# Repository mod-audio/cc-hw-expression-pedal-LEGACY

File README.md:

Legacy mod-hw-expression-pedal
=======================

This repository contains the schematics and PCB design files for the Expression Pedal hardware.
This is a peripheral meant to be used in conjunction with MOD (http://moddevices.com/) via its control-chain interface.

These files were created and can be improved with KiCAD, a free software Electronics CAD which is available at http://www.kicad-pcb.org/

## Check out instructions ##

This project uses a set of KiCAD symbols and footprints provided by the official KiCad library (https://github.com/KiCad/). In order to properly fetch these dependencies, which are configured as submodule repositories, you have to use the **--recursive** attribute in the following **git** command:

> git clone --recursive https://github.com/mod-audio/cc-hw-expression-pedal-LEGACY.git

## Licensing ##

Copyright (c) 2014-2026 MOD Audio Limited.

The hardware design files (schematics, PCB layouts, fabrication files, BOMs) are licensed under
[CC BY-SA 4.0](https://creativecommons.org/licenses/by-sa/4.0/) (see [`LICENSE`](LICENSE)).
This is an open hardware project: you may use, modify, build and sell it, as long as you credit MOD Audio
and share your modified design files under the same licence.

Third-party files (manufacturer component models, library parts, supplier documents) are not covered by
this licence. See [`NOTICE`](NOTICE) for the list.

The MOD logo is a registered trademark (EU trade mark no. 016228827; UK trade mark no. UK00916228827).
The licence gives no right to use the MOD name or logo. See [`NOTICE`](NOTICE).

## Firmware ##

The firmware is kept in a separate repository and is not part of this one.

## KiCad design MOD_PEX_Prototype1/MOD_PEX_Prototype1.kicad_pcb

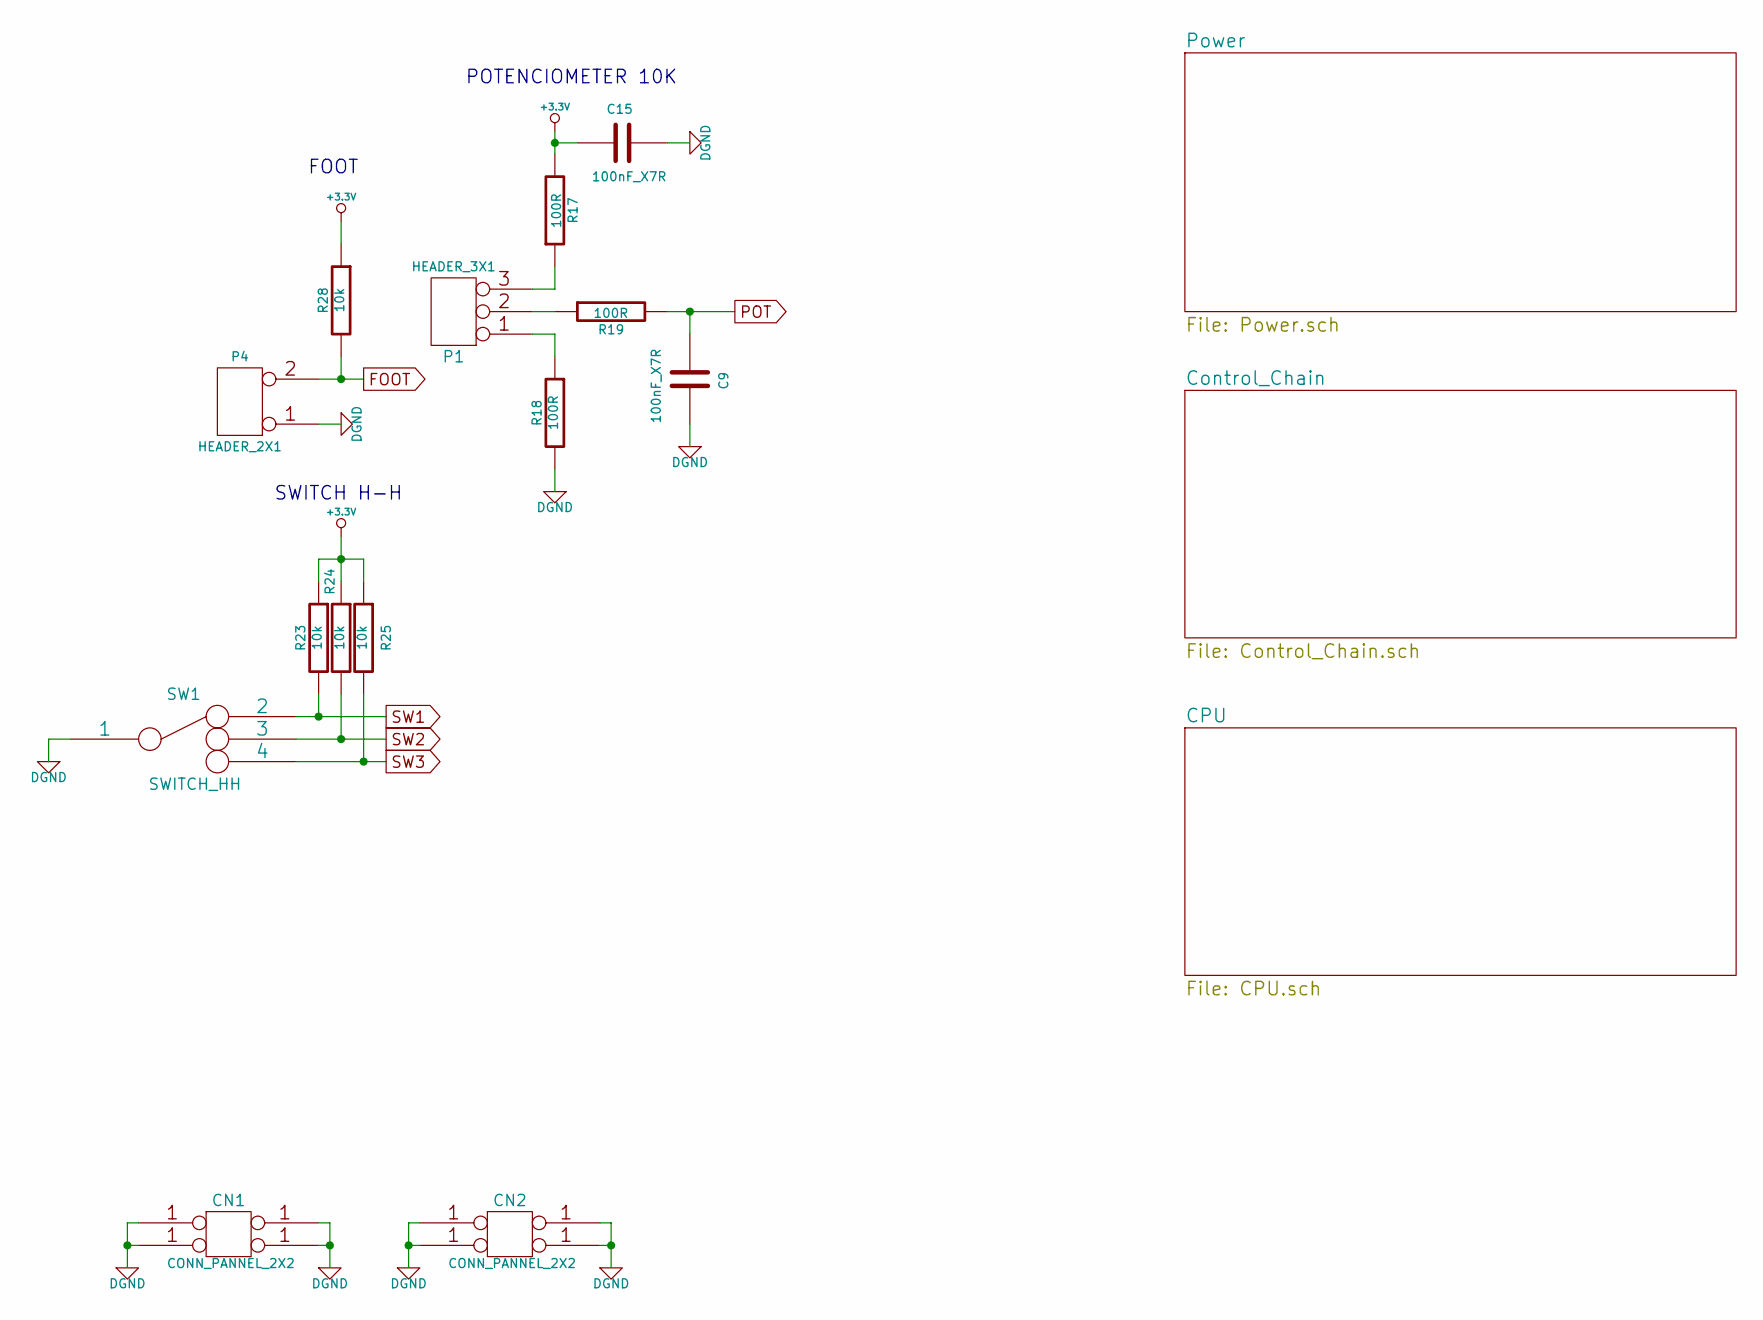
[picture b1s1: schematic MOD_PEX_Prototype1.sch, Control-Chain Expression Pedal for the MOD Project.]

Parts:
C9, C15: 100nF_X7R; SM0603
CN1, CN2: CONN_PANNEL_2X2; CONN_PANNEL
P1: HEADER_3X1; PIN_ARRAY_3X1
P4: HEADER_2X1; PIN_ARRAY_2X1
R17, R18, R19: 100R; SM0603
R23, R24, R25, R28: 10k; SM0603
SW1: SWITCH_HH; SWITCH_HH_SK-13D26-G-6_5-K-GY

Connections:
DGND: C9.2, C15.2, CN1.1, CN2.1, P4.1, R18.2, SW1.1; also elsewhere on the board
FOOT: P4.2 (PM), R28.2; also elsewhere on the board
unnamed: P1.1, R18.1
unnamed: P1.2 (PM), R19.1
unnamed: P1.3, R17.1
POT: C9.1, R19.2; also elsewhere on the board
SW1: R23.2, SW1.2; also elsewhere on the board
SW2: R24.2, SW1.3; also elsewhere on the board
SW3: R25.2, SW1.4; also elsewhere on the board

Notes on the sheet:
POTENCIOMETER 10K
SWITCH H-H
FOOT

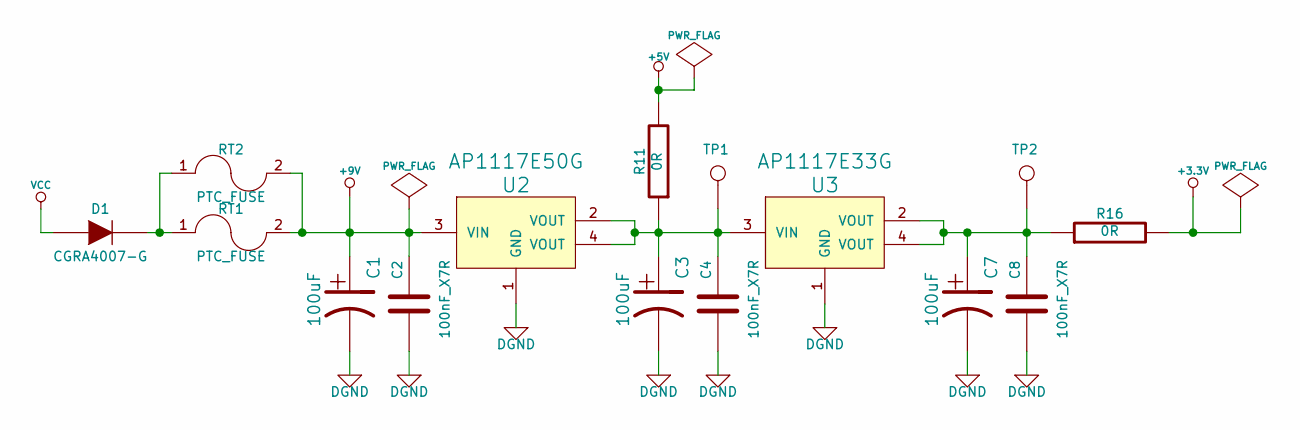
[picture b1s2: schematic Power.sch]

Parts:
C1, C3, C7: 100uF; CAP_RAD_5MM
C2, C4, C8: 100nF_X7R; SM0603
D1: CGRA4007-G; DO-214AC(SMA)
R11, R16: 0R; SM0805
RT1: PTC_FUSE; SM1210
RT2: PTC_FUSE; SM2920
TP1, TP2: CONN_1; SIL-1
U2: AP1117E50G; SOT223_3
U3: AP1117E33G; SOT223_3

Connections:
+5V: R11.2; also elsewhere on the board
+9V: C1.1, C2.1, RT1.2, RT2.2, U2.3 (VIN)
DGND: C1.2, C2.2, C3.2, C4.2, C7.2, C8.2, U2.1 (GND), U3.1 (GND); also elsewhere on the board
unnamed: C3.1, C4.1, R11.1, TP1.1, U2.2 (VOUT), U2.4 (VOUT), U3.3 (VIN)
unnamed: C7.1, C8.1, R16.1, TP2.1, U3.2 (VOUT), U3.4 (VOUT)
unnamed: D1.2 (K), RT1.1, RT2.1
VCC: D1.1 (A); also elsewhere on the board

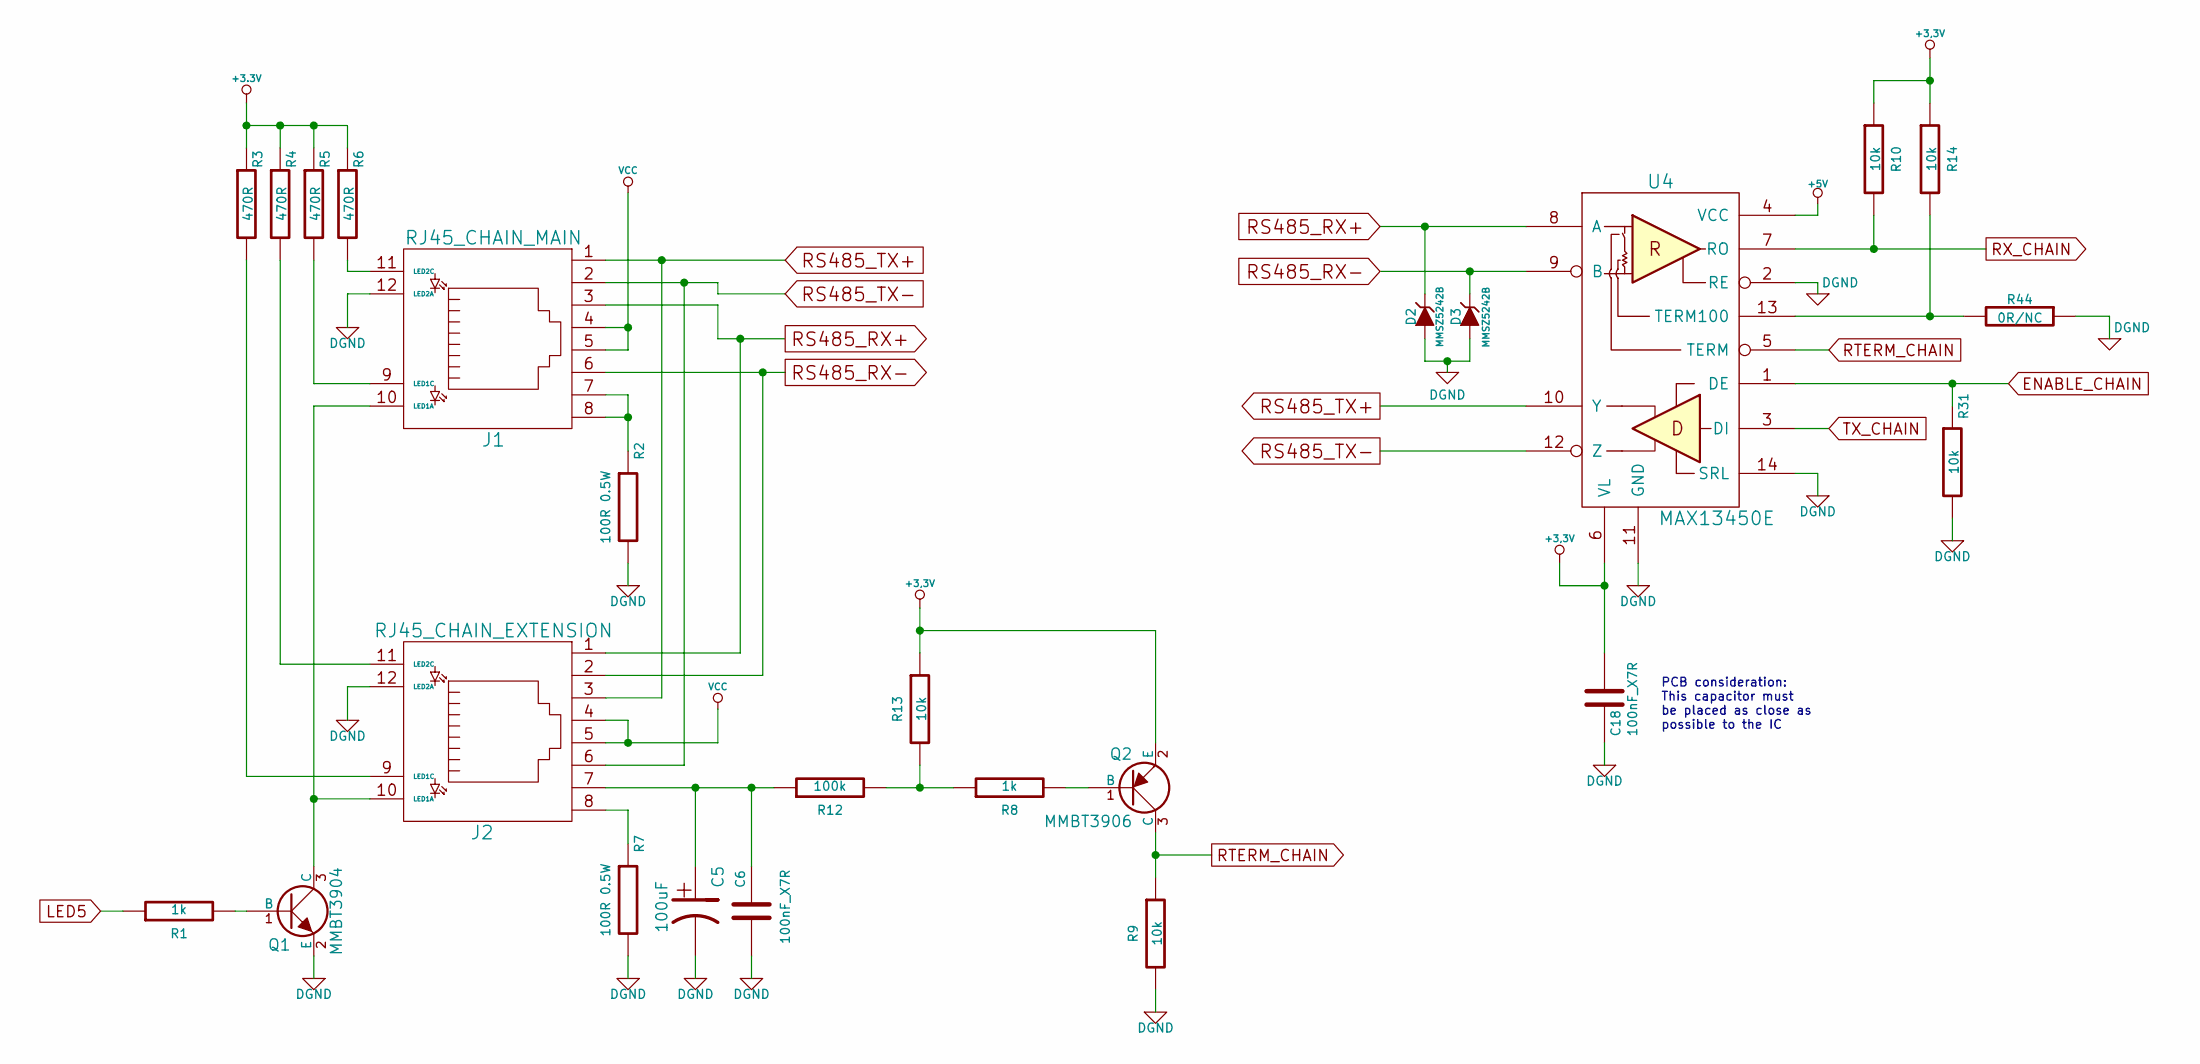
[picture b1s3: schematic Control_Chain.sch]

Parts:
C5: 100uF; CAP_RAD_5MM
C6, C18: 100nF_X7R; SM0603
D2, D3: MMSZ5242B; SOD123
J1: RJ45_CHAIN_MAIN; RJ45-RJHSE5084
J2: RJ45_CHAIN_EXTENSION; RJ45-RJHSE5084
Q1: MMBT3904; SOT23
Q2: MMBT3906; SOT23
R1, R8: 1k; SM0603
R2, R7: 100R 0.5W; SM1210
R3, R4, R5, R6: 470R; SM0805
R9, R10, R13, R14, R31: 10k; SM0603
R12: 100k; SM0603
R44: 0R/NC; SM0805
U4: MAX13450E; TSSOP14

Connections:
+5V: U4.4 (VCC); also elsewhere on the board
DGND: C5.2, C6.2, C18.2, D2.1 (A), D3.1 (A), J1.12 (LED2A), J2.12 (LED2A), Q1.2 (E), R2.2, R7.2, R9.2, R31.2, R44.1, U4.2 (RE), U4.11 (GND), U4.14 (SRL); also elsewhere on the board
ENABLE_CHAIN: R31.1, U4.1 (DE); also elsewhere on the board
LED5: R1.1
unnamed: C5.1, C6.1, J2.7, R12.1
unnamed: J1.7, J1.8, R2.1
unnamed: J1.9 (LED1C), R5.2
unnamed: J1.10 (LED1A), J2.10 (LED1A), Q1.3 (C)
unnamed: J1.11 (LED2C), R6.2
unnamed: J2.8, R7.1
unnamed: J2.9 (LED1C), R3.2
unnamed: J2.11 (LED2C), R4.2
unnamed: Q1.1 (B), R1.2
unnamed: Q2.1 (B), R8.2
unnamed: R8.1, R12.2, R13.2
unnamed: R14.2, R44.2, U4.13 (TERM100)
RS485_RX+: D2.2 (K), J1.3, J2.1, U4.8 (A)
RS485_RX-: D3.2 (K), J1.6, J2.2, U4.9 (B)
RS485_TX+: J1.1, J2.3, U4.10 (Y)
RS485_TX-: J1.2, J2.6, U4.12 (Z)
RTERM_CHAIN: Q2.3 (C), R9.1, U4.5 (TERM)
RX_CHAIN: R10.2, U4.7 (RO); also elsewhere on the board
TX_CHAIN: U4.3 (DI); also elsewhere on the board
VCC: J1.4, J1.5, J2.4, J2.5; also elsewhere on the board

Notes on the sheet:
PCB consideration: This capacitor must be placed as close as possible to the IC

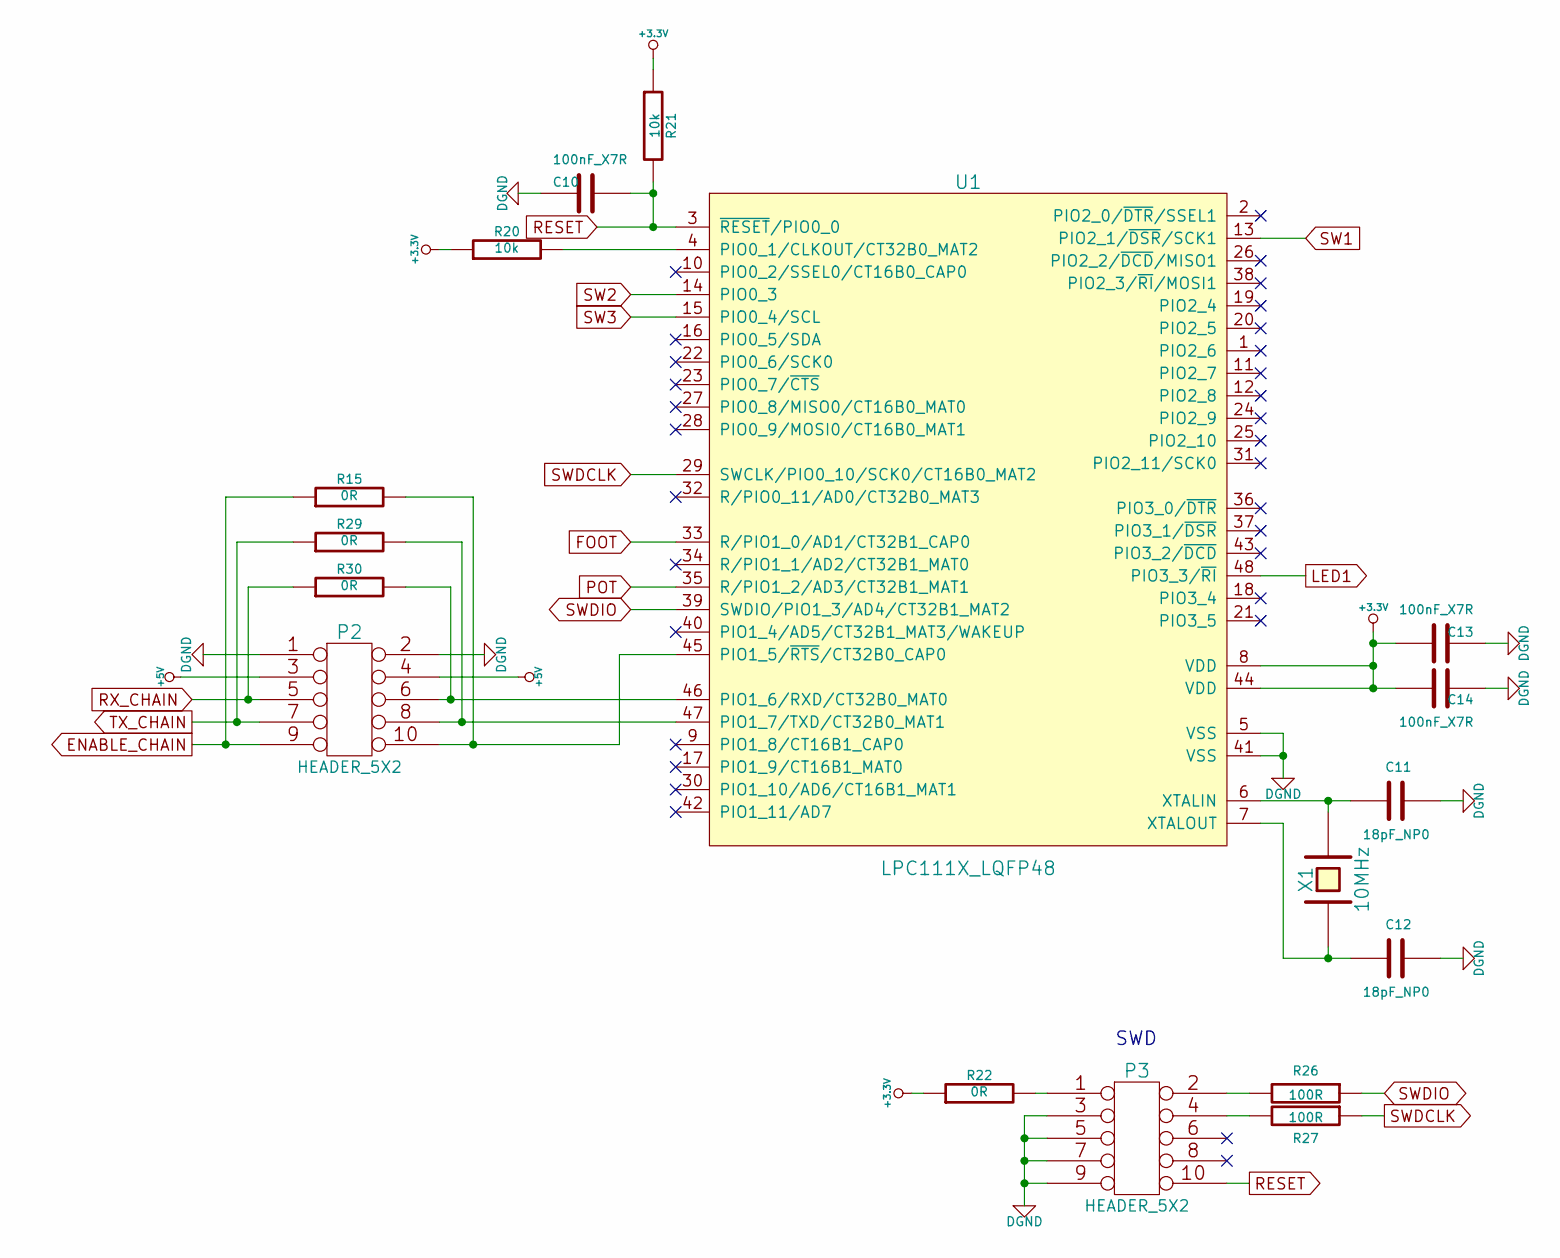
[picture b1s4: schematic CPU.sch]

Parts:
C10, C13, C14: 100nF_X7R; SM0603
C11, C12: 18pF_NP0; SM0603
P2, P3: HEADER_5X2; PIN_ARRAY_5x2
R15, R22, R29, R30: 0R; SM0603
R20, R21: 10k; SM0603
R26, R27: 100R; SM0603
U1: LPC111X_LQFP48; LQFP48
X1: 10MHz; HC_49US

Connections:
+5V: P2.3, P2.4; also elsewhere on the board
DGND: C10.2, C11.1, C12.1, C13.2, C14.2, P2.1, P2.2, P3.3, P3.5, P3.7, P3.9, U1.5 (VSS), U1.41 (VSS); also elsewhere on the board
ENABLE_CHAIN: P2.9, R15.1; also elsewhere on the board
FOOT: U1.33 (R/PIO1_0/AD1/CT32B1_CAP0); also elsewhere on the board
LED1: U1.48 (PIO3_3/~RI)
unnamed: C11.2, U1.6 (XTALIN), X1.2
unnamed: C12.2, U1.7 (XTALOUT), X1.1
unnamed: P2.6, R30.2, U1.46 (PIO1_6/RXD/CT32B0_MAT0)
unnamed: P2.8, R29.2, U1.47 (PIO1_7/TXD/CT32B0_MAT1)
unnamed: P2.10, R15.2, U1.45 (PIO1_5/~RTS~/CT32B0_CAP0)
unnamed: P3.1, R22.2
unnamed: P3.2, R26.2
unnamed: P3.4, R27.2
unnamed: R20.2, U1.4 (PIO0_1/CLKOUT/CT32B0_MAT2)
POT: U1.35 (R/PIO1_2/AD3/CT32B1_MAT1); also elsewhere on the board
RESET: C10.1, P3.10, R21.2, U1.3 (~RESET~/PIO0_0)
RX_CHAIN: P2.5, R30.1; also elsewhere on the board
SW1: U1.13 (PIO2_1/~DSR~/SCK1); also elsewhere on the board
SW2: U1.14 (PIO0_3); also elsewhere on the board
SW3: U1.15 (PIO0_4/SCL); also elsewhere on the board
SWDCLK: R27.1, U1.29 (SWCLK/PIO0_10/SCK0/CT16B0_MAT2)
SWDIO: R26.1, U1.39 (SWDIO/PIO1_3/AD4/CT32B1_MAT2)
TX_CHAIN: P2.7, R29.1; also elsewhere on the board

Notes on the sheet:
SWD

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
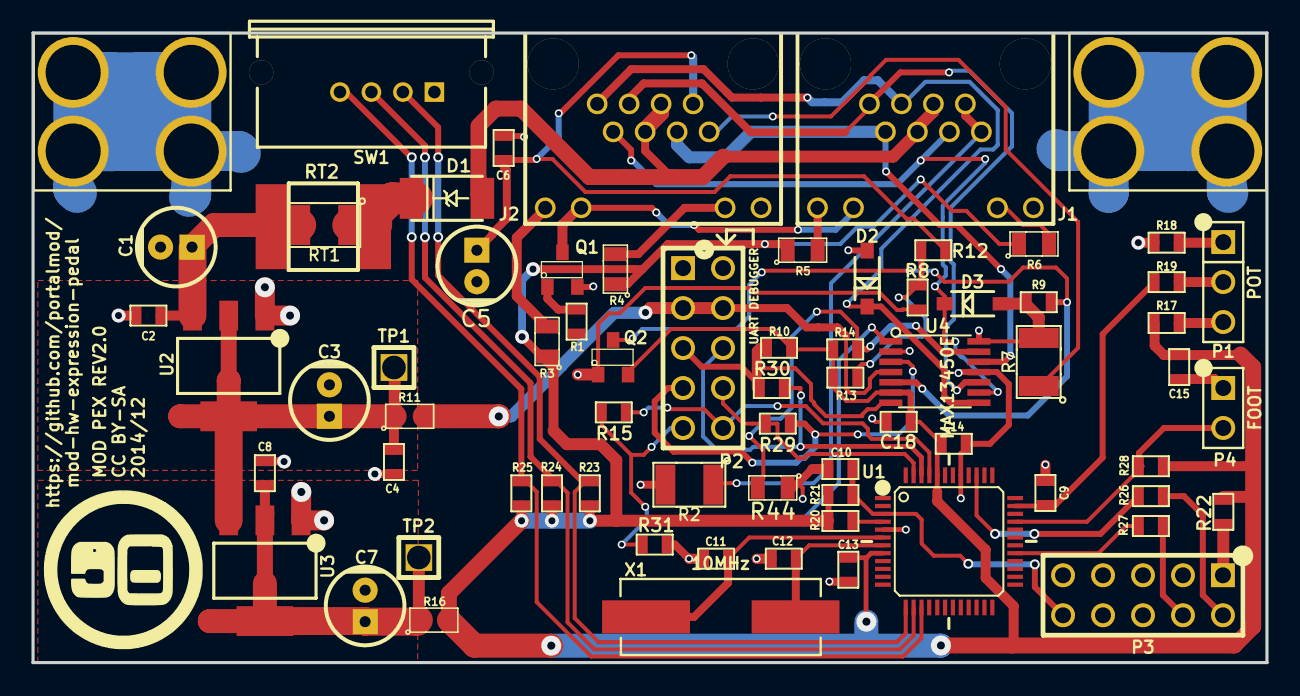
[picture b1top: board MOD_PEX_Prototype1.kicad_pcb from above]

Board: 2 copper layers, 78.4 x 40.0 mm, 71 parts (0 on the bottom side), 48 nets.

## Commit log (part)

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2014-05-15 Initial commit of MOD PEX (MOD Expression Pedal) hardware project.
2014-06-03 BOM for ITEAD quotes.
2014-06-16 Created BOM with ITEAD template.
2014-12-01 Add a README.md and fix issue #1 (Declaring CC-By-SA licensing)
2014-12-01 Adding metadata to the schematics drawing (fix issue #5) and improving the PCB grounding by attaching CN1 and CN2 to the DGND copper plane (fix issue #4).
2014-12-01 Added a README.md reference to the firmware source code repository. (fixes issue #2)
2014-12-03 updating gerber files
2014-12-03 removing spare ITEAD directory (which contained redundant copies of gerber files)
2014-12-03 updating netlist and kicad_pcb
2014-12-03 adding mod-kicad-footprints as a git submodule (and documenting it in the README)
2014-12-03 updating footprints (to use the ones from the mod-kicad-footprints repository)
2014-12-03 updating Gerbers
2014-12-05 Bringing back the positioning of references and values that were messed up by the recent refactoring of footprint libraries.
2014-12-09 wip on issue #7: protect the U4 IC when the board is being debugged Made the necessary changes in the schematics drawing.
2014-12-09 fix issue #7: protect the U4 IC when the board is being debugged updated the pcb traces and Gerber outputs.
2014-12-09 wip on issue #9: change footprint of RT1 I'm adding a second footprint so that we have 2 choices of fuse packages we can use: SM2920 or SM1210
2014-12-09 fix issue #9: change footprint of RT1 (updated pcb traces and gerber outputs)
2014-12-09 fix issue #3: Add "CC by-SA" license logo to the PCB silk layer I have adapted and rearranged the previous silk text as well.
2014-12-12 wip on issue #11: Use the same control chain circuit of the footswitch separated the schematics in subsheets and added the new control chain circuit and schematic symbols
2014-12-12 wip issue #11: tracing the PCB signals
2014-12-15 Fixing control chain signal names, adding a 0R resistor for the ENABLE_CHAIN signal in the P1 debugging connector and regenerating the netlist.
2014-12-15 fix issue #11 (new control chain circuitry): tracing the PCB to incorporate schematics changes.
2014-12-15 fixing footprint and labels positioning.
2014-12-15 updating a few 3d model settings
2014-12-16 Adding a local copy of a few 3d models of components and using the TQFP48 one. Also fixing the references to the 3d models from the kicad-common deb-package.
2014-12-16 fixing the component packages for SMD resistors (3d modules)
2014-12-17 wip issue #12: Use 3.3V for Lv in the control chain circuit
2014-12-17 fix issue #12: Use 3.3V for Lv in the control chain circuit (updated the pcb layout and regenerated gerber files)
2014-12-18 plotting the schematics to a PDF to be kept in the Docs directory (we should always update this PDF when we make changes to the schematics).
2015-01-07 Moving schematics component symbols to an external git submodule.
2015-01-07 Moving the Docs directory to the root dir of the repository.
2015-01-12 removing unused libraries
2015-01-12 renaming control chain sheet
2015-01-12 updating control chain circuit
2015-01-30 renaming project
2015-01-30 moving I/O stuff to new sheet
2015-02-07 renaming sch files
2015-02-17 changing cpu schematic to use default kicad components library
2015-02-18 changing I/O schematic to use default kicad components library
2015-02-18 changing power schematic to use default kicad components library
2015-02-18 changing control chain schematic to use default kicad components library
2015-02-18 adding libraries
2015-02-18 ERC passing
2015-02-19 removing one of the fuses
2015-02-27 wip: footprint association using default kicad libraries
2015-06-03 adding official kicad library as submodule
2015-06-03 replacing some cached symbols by kicad-library symbols
2015-06-03 setting up submodules
2015-06-03 sch: updating some cached symbols
2015-06-03 moving files inside board dir
2015-06-03 sch: setting lib paths and adding local-library
2015-06-09 sch: load switch circuit sketch
2015-06-09 sch: updating local library
2015-06-09 sch: control chain circuit (wip)
2015-06-10 sch: control chain circuit
2015-06-10 power circuit done
2015-06-10 sch: cpu reset done (wip)
2015-06-11 sch: cpu, I/Os and control chain circuits done
2015-06-11 sch: library cache updated
2015-06-11 sch: schematic annotation done
2015-06-11 sch: errors fixed, DRC passing
2015-06-11 sch: adding values and MPN to components
2015-06-11 sch: BOM created
2015-06-11 sch: JTAG connector footprint fixed
2015-06-12 sch: MOSFET MPN fixed
2015-06-23 sch: setting footprints and updating BOM
2015-06-23 footprints dependencies added to submodules
2015-06-23 fixing some footprints assignment
2015-06-23 README updated
2015-06-23 unused submodule removed
2015-06-25 sch: fixing VBUS signal and FS1 I/O
2015-06-25 BOM updated
